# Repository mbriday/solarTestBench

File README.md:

# Solar Panel Test Bench

A programmable LED illumination bench for testing solar panels used in low-power embedded systems under controlled, repeatable lighting conditions.

## Features

- **Eight LED channels**, driven by PWM at **259 kHz**. The channels are evenly phase-shifted by **1/8 of a period** to minimize fluctuations in the combined light output.
- **Programmable lighting scenarios** to reproduce varying illumination conditions.
- **Wi-Fi connectivity** using a Raspberry Pi Pico W.

## Repository structure

- `board/`: KiCad files for the main PCB. See `board/README.md` for modifications done after the first PCB batch.
- `firmware/`: Arduino firmware for the Pico W. See the `.ino` file for dependencies and setup instructions.

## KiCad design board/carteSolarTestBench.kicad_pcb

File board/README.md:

Each PWM device has 2 outputs. To enable PWMs to be dephased, each output must be on a dedicated device.

The following changes need to be made to the PCB:

|signal |     pin     | Channel |  todo                                                     |
|-------|-------------|---------|-----------------------------------------------------------|
| pwmL1 | GP8  → GP2  | `1A`    | pin 11 cut and connect to U2                              |
| pwmL2 | GP9  → GP9  | `4B`    | -                                                         |
| pwmL3 | GP6  → GP6  | `3A`    | -                                                         |
| pwmL4 | GP7  → GP0  | `0A`    | pin 10 cut B <-> pin 1 cut B (fan0). connect to R2 and U6 |
| pwmL5 | GP10 → GP10 | `5A`    | -                                                         |
| pwmL6 | GP11 → GP15 | `7B`    | cut pin 15 B and connect pin 20 to U3                     |
| pwmL7 | GP12 → GP20 | `2B`    | cut pin 16 and connect pin 26 to U4                       |
| pwmL8 | GP13 → GP13 | `6B`    | -                                                         |

As a consequence:
|Fan    |  todo                                                                   |
|-------|-------------------------------------------------------------------------|
| fan 0 | now on pin 10 (GP7), PWM device `3B`… with the same freq as GP6 → pwmL3 |
| fan 1 | unchanged on GP1, PWM device `0B`, with same freq as GP0 → pwmL4        |

```c
const int lineToPWM[] = {1,4,3,0,5,7,2,6};
```

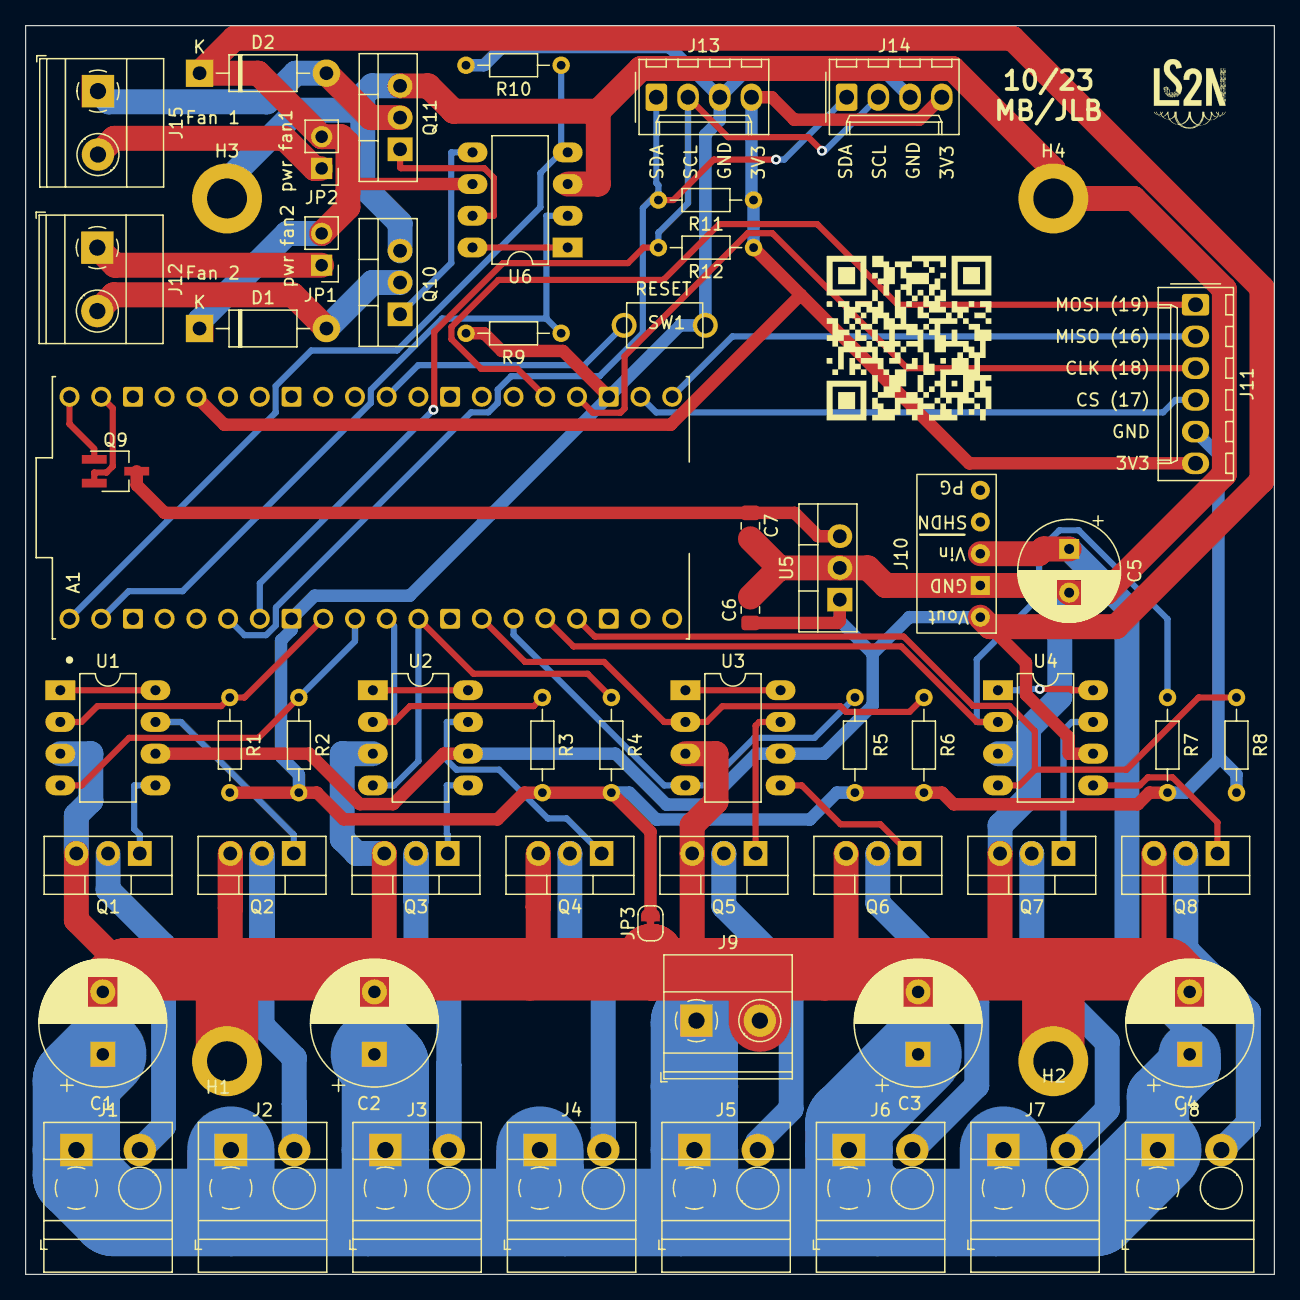
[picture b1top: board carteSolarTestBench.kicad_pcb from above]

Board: 2 copper layers, 100.0 x 100.0 mm, 63 parts (0 on the bottom side), 47 nets.

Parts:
A1: SC0918; MODULE_SC0918
C1, C2, C3, C4: 470uF; CP_Radial_D10.0mm_P5.00mm
C5: 47uF; CP_Radial_D8.0mm_P3.50mm
C6: 0.33uF; C_0805_2012Metric_Pad1.18x1.45mm_HandSolder
C7: 0.1uF; C_0805_2012Metric_Pad1.18x1.45mm_HandSolder
D1, D2: 1N4001; D_DO-41_SOD81_P10.16mm_Horizontal
GLogo: LOGO; qrCodeSolarTestBench
H1, H2, H3, H4: MountingHole_Pad; MountingHole_3.2mm_M3_DIN965_Pad
J1, J2, J3, J4, J5, J6, J7, J8: Screw_Terminal_01x02; connecteur_TME_2EDGRC5-08-2P14
J9, J12, J15: Screw_Terminal_01x02; TerminalBlock_Phoenix_MKDS-1,5-2-5.08_1x02_P5.08mm_Horizont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
J10: Pololu D24V10F12; pololu_2834
J11: Conn_01x06_Male; Molex_KK-254_AE-6410-06A_1x06_P2.54mm_Vertical
J13, J14: Conn_01x04_Male; Molex_KK-254_AE-6410-04A_1x04_P2.54mm_Vertical
JP1, JP2: Jumper_2_Bridged; PinHeader_1x02_P2.54mm_Vertical
JP3: SolderJumper_2_Bridged; SolderJumper-2_P1.3mm_Bridged_RoundedPad1.0x1.5mm
Q1, Q2, Q3, Q4, Q5, Q6, Q7, Q8, Q10, Q11: IRF540N; TO-220-3_Vertical
Q9: DMG2305UX-13; SOT-23W_Handsoldering
R1, R2, R3, R4, R5, R6, R7, R8, R9, R10: 10K; R_Axial_DIN0204_L3.6mm_D1.6mm_P7.62mm_Horizontal
R11, R12: 2.2K; R_Axial_DIN0204_L3.6mm_D1.6mm_P7.62mm_Horizontal
SW1: SW_Push; pushButton
U1, U2, U3, U4, U6: TC4424EPA; DIP-8_W7.62mm_LongPads
U5: L7805; TO-220-3_Vertical

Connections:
+5V: C7.1, Q9.3 (D), U5.3 (OUT)
+12V: C6.1, D1.1 (K), D2.1 (K), J10.1, JP1.2 (B), JP2.2 (B), U1.6 (VDD), U2.6 (VDD), U3.6 (VDD), U4.6 (VDD), U5.1 (IN), U6.6 (VDD)
+24V: C1.1, C2.1, C3.1, C4.1, C5.1, J1.1, J2.1, J3.1, J4.1, J5.1, J6.1, J7.1, J8.1, J9.1, J10.3
/3V3: A1.36 (3V3_OUT), J11.6, J13.4, J14.4, R11.1, R12.1
/+12Fan1: J12.1, JP1.1 (A)
/+12Fan2: J15.2, JP2.1 (A)
/MISO: A1.21 (GP16), J11.2
/MOSI: A1.25 (GP19), J11.1
/SCL: A1.7 (GP5), J13.2, J14.2, R12.2
/SDA: A1.6 (GP4), J13.1, J14.1, R11.2
/SPI_CLK: A1.24 (GP18), J11.3
/SPI_CS: A1.22 (GP17), J11.4
/alimLed/pwr_led1: J1.2, Q1.2 (D)
/alimLed/pwr_led2: J2.2, Q2.2 (D)
/alimLed/pwr_led3: J3.2, Q3.2 (D)
/alimLed/pwr_led4: J4.2, Q4.2 (D)
/alimLed/pwr_led5: J5.2, Q5.2 (D)
/alimLed/pwr_led6: J6.2, Q6.2 (D)
/alimLed/pwr_led7: J7.2, Q7.2 (D)
/alimLed/pwr_led8: J8.2, Q8.2 (D)
/cmvVentilo1: D1.2 (A), J12.2, Q10.2 (D)
/cmvVentilo2: D2.2 (A), J15.1, Q11.2 (D)
/pwmL1: A1.11 (GP8), R3.1, U2.2 (IN_A)
/pwmL2: A1.12 (GP9), R4.1, U2.4 (IN_B)
/pwmL3: A1.9 (GP6), R1.1, U1.2 (IN_A)
/pwmL4: A1.10 (GP7), R2.1, U1.4 (IN_B)
/pwmL5: A1.14 (GP10), R6.1, U3.2 (IN_A)
/pwmL6: A1.15 (GP11), R5.1, U3.4 (IN_B)
/pwmL7: A1.16 (GP12), R7.1, U4.2 (IN_A)
/pwmL8: A1.17 (GP13), R8.1, U4.4 (IN_B)
/pwmVentilo1: A1.1 (GP0), R10.1, U6.4 (IN_B)
/pwmVentilo2: A1.2 (GP1), R9.1, U6.2 (IN_A)
GND: A1.8 (GND), A1.23 (GND), J11.5, J13.3, J14.3, JP3.2 (B), R1.2, R2.2, R3.2, R4.2, R5.2, R6.2, R7.2, R8.2, R9.2, R10.2, SW1.2
GNDPWR: C1.2, C2.2, C3.2, C4.2, C5.2, C6.2, C7.2, H1.1, H2.1, H3.1, H4.1, J9.2, J10.2, JP3.1 (A), Q1.3 (S), Q2.3 (S), Q3.3 (S), Q4.3 (S), Q5.3 (S), Q6.3 (S), Q7.3 (S), Q8.3 (S), Q10.3 (S), Q11.3 (S), U1.3 (GND), U2.3 (GND), U3.3 (GND), U4.3 (GND), U5.2 (GND), U6.3 (GND)
unnamed: A1.30 (RUN), SW1.1
unnamed: A1.39 (VSYS), Q9.2 (S)
unnamed: A1.40 (VBUS), Q9.1 (G)
unnamed: Q1.1 (G), U1.5 (OUT_B)
unnamed: Q2.1 (G), U1.7 (OUT_A)
unnamed: Q3.1 (G), U2.5 (OUT_B)
unnamed: Q4.1 (G), U2.7 (OUT_A)
unnamed: Q5.1 (G), U3.7 (OUT_A)
unnamed: Q6.1 (G), U3.5 (OUT_B)
unnamed: Q7.1 (G), U4.7 (OUT_A)
unnamed: Q8.1 (G), U4.5 (OUT_B)
unnamed: Q10.1 (G), U6.5 (OUT_B)
unnamed: Q11.1 (G), U6.7 (OUT_A)
